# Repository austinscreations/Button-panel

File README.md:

# Button-panel
Low cost RGB button panel for home automation - based off superhouse.tv switch setup

After seeing the new RGB switch panels that jon from superhouse.tv is making the thing that has been noted is the switches cost a fair bit of money. 

I thought it might be possible to 3d print parts and use clear acrylic tubing / rod to create low cost versions of teh panels.
To start I've designed two PCB's one has 4 leds per button to emulate teh current ring light buttons
the second version uses one center led for a cenetr lighting in the button - acyrlic rod would be inserted into a 3d print.

Once I have a chance I plan to produce the pcb and order parts on ebay and create the 3d print assemblies to see what teh cost would be and if it works well.

2021-09-07
added a node-red demo taht hsows all the functions nicely.
added to and bottom photos of pcb along with pinout for RX / TX

2021-07-08
Working full code for type-1 assembly has been added. Now has working button deboucing and outputs teh same json type string as the superhouse.tv LSC project.
New PCB's has been produced and is working correctly with new code - files might need to be updated here...

2021-04-28
Added the latest version. will order parts soon to test the design.
Added a new 3d model for an AUS plate, design is incomplete and will get my hands on a real one to adjust the model as needed.

2021-04-23 
added code that will be used during livestream. haven't got tasmota to control the lights correctly yet; thus will be using custom code

2021-04-22
PCB's arrived which means I'll be doing a livestream of their assembly and testing https://youtu.be/Dpo3wsEXy4c

2021-04-18
Updated 3d files to fit around capacitors and ethernet connector. The 3d files and pcb's will be re-layed out to fix these in the next version. allowing for faster 3d printing, vs having holes / cutouts made.

2021-04-16
I've ordered PCB's to test. 
Created 3d photo of pcb assemblies. Next versions will use esp8266 direct vs D1 mini.
Cost Sheet updated.

2020-12-12
reformated files
added new version 2 which makes the pcb compact - allows for 24mm spacing between each button matching the assembly of teh superhouse button panels - it allso allowed for teh buttons to be centered on a wall plate. wall plate is normal cover / size for single gang north america box
3D step files for each button design assembly has been added - these are untested - no parts on order yet.
future possible version my have the 0.1mm pitch conenctor to match up to the new superhouse tv RGB button assembly.

2020-12-04
updating pcb files as the 1000uf capacitor was the wrong size (footprint is now 10x10mm)
adding photos of the pcb for both versions
added parts list for both versions
added rough cost breakdown of buying parts on ebay

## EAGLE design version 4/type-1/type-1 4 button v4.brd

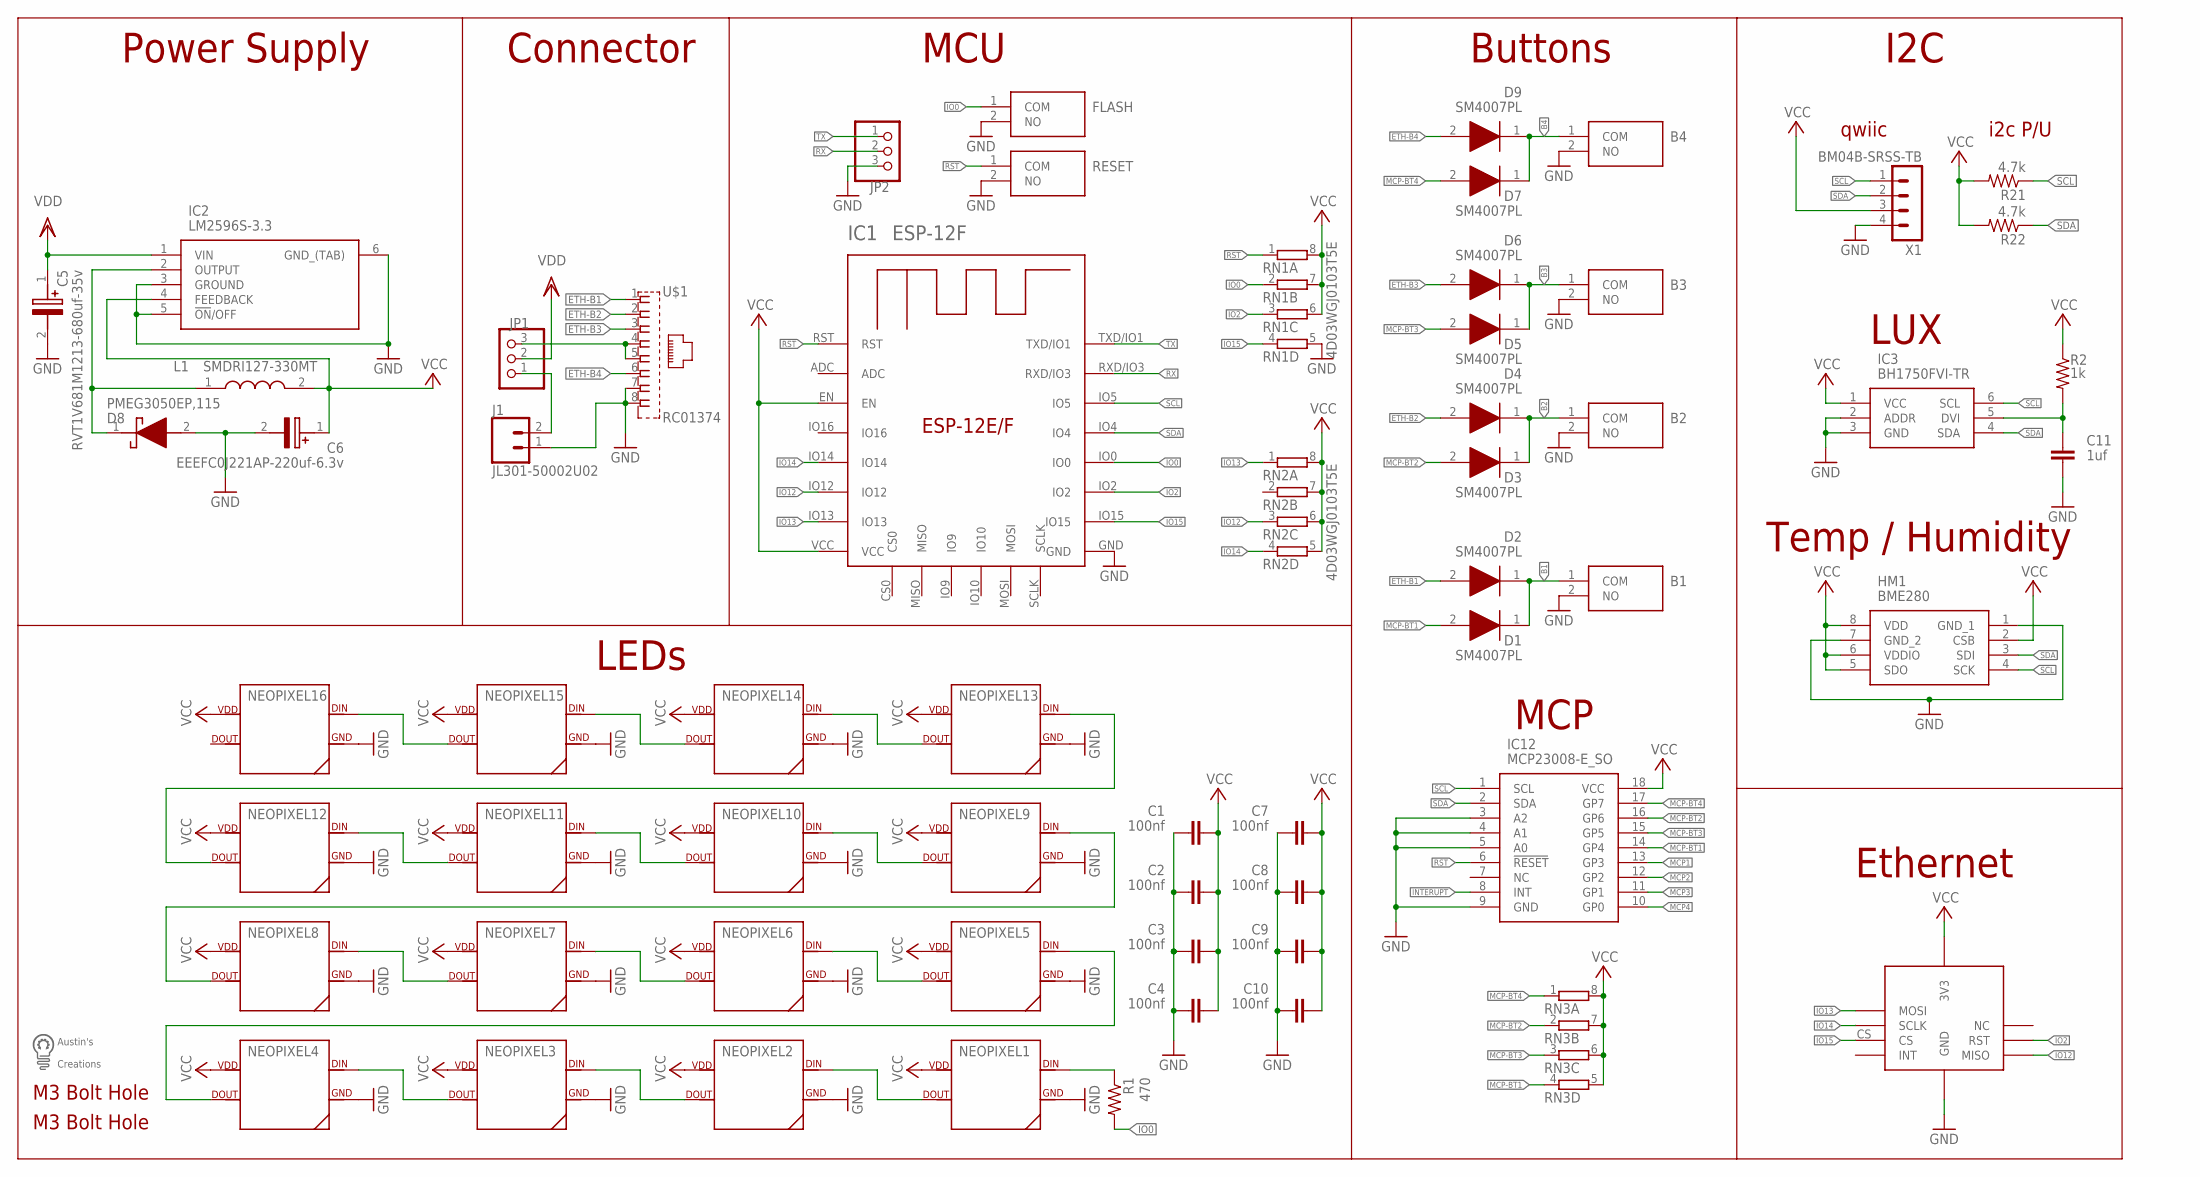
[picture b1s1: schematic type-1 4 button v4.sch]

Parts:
B1, B2, B3, B4: PTS636_SM25F_SMTR_LFS; PTS636SM25FSMTRLFS
C1, C2, C3, C4, C7, C8, C9, C10: 100nf; C0603
C5: RVT1V681M1213-680uf-35v; CAPAE1350X1400N
C6: EEEFC0J221AP-220uf-6.3v; CAPAE830X650N
C11: 1uf; C0603
D1, D2, D3, D4, D5, D6, D7, D9: SM4007PL; SODFL3718X125N
D8: PMEG3050EP,115; PMEG3050EP115
FLASH: PTS636_SM25F_SMTR_LFS; PTS636SM25FSMTRLFS
HM1: BME280
IC1: ESP-12F; ESP-12E
IC2: LM2596S-3.3; TO170P1435X465-6N
IC3: BH1750FVI-TR; WSOF6
IC12: MCP23008-E_SO; SOIC127P1030X265-18N
J1: JL301-50002U02; SCREWTERMINAL-5MM-2
JP1, JP2: PINHD-1X3; 1X03
L1: SMDRI127-330MT; INDPM120120X800N
NEOPIXEL1, NEOPIXEL2, NEOPIXEL3, NEOPIXEL4, NEOPIXEL5, NEOPIXEL6, NEOPIXEL7, NEOPIXEL8, NEOPIXEL9, NEOPIXEL10, NEOPIXEL11, NEOPIXEL12, NEOPIXEL13, NEOPIXEL14, NEOPIXEL15, NEOPIXEL16: SK6812NEOPIXEL5050; SK6812
R1: 470; R0603
R2: 1k; R0603
R21, R22: 4.7k; R0603
RESET: PTS636_SM25F_SMTR_LFS; PTS636SM25FSMTRLFS
RN1, RN2, RN3: 4R-N0603-ARC; 0603-ARC
U$1: RC01374
U$3: W5500MODULE
U$4, U$5: M3BOLTHOLE
U$6: LOGOMED
X1: BM04B-SRSS-TB

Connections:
B1: B1.1 (COM), D1.1 (K), D2.1 (K)
B2: B2.1 (COM), D3.1 (K), D4.1 (K)
B3: B3.1 (COM), D5.1 (K), D6.1 (K)
B4: B4.1 (COM), D7.1 (K), D9.1 (K)
ETH-B1: D2.2 (A), U$1.1
ETH-B2: D4.2 (A), U$1.2
ETH-B3: D6.2 (A), U$1.3
ETH-B4: D9.2 (A), U$1.6
GND: B1.2 (NO), B2.2 (NO), B3.2 (NO), B4.2 (NO), C1.1, C2.1, C3.1, C4.1, C5.2 (-), C6.2 (-), C7.1, C8.1, C9.1, C10.1, C11.2, D8.2 (A), FLASH.2 (NO), HM1.1 (GND_1), HM1.7 (GND_2), IC1.GND, IC2.3 (GROUND), IC2.5 (!ON!/OFF), IC2.6 (GND_(TAB)), IC3.2 (ADDR), IC3.3 (GND), IC12.3 (A2), IC12.4 (A1), IC12.5 (A0), IC12.9 (GND), J1.1, JP2.3, NEOPIXEL1.3 (GND), NEOPIXEL2.3 (GND), NEOPIXEL3.3 (GND), NEOPIXEL4.3 (GND), NEOPIXEL5.3 (GND), NEOPIXEL6.3 (GND), NEOPIXEL7.3 (GND), NEOPIXEL8.3 (GND), NEOPIXEL9.3 (GND), NEOPIXEL10.3 (GND), NEOPIXEL11.3 (GND), NEOPIXEL12.3 (GND), NEOPIXEL13.3 (GND), NEOPIXEL14.3 (GND), NEOPIXEL15.3 (GND), NEOPIXEL16.3 (GND), RESET.2 (NO), RN1.5 (2), U$1.7, U$1.8, U$3.GND1 (GND), U$3.GND2 (GND), U$3.GND3 (GND), X1.4
INTERUPT: IC12.8 (INT)
IO0: FLASH.1 (COM), IC1.IO0, R1.2, RN1.2 (1)
IO2: IC1.IO2, RN1.3 (1), U$3.RST
IO12: IC1.IO12, RN2.3 (1), U$3.MISO
IO13: IC1.IO13, RN2.1, U$3.MOSI
IO14: IC1.IO14, RN2.4 (1), U$3.SCLK
IO15: IC1.IO15, RN1.4 (1), U$3.CS
MCP1: IC12.13 (GP3)
MCP2: IC12.12 (GP2)
MCP3: IC12.11 (GP1)
MCP4: IC12.10 (GP0)
MCP-BT1: D1.2 (A), IC12.14 (GP4), RN3.4 (1)
MCP-BT2: D3.2 (A), IC12.16 (GP6), RN3.2 (1)
MCP-BT3: D5.2 (A), IC12.15 (GP5), RN3.3 (1)
MCP-BT4: D7.2 (A), IC12.17 (GP7), RN3.1
unnamed: NEOPIXEL1.4 (DIN), R1.1
unnamed: NEOPIXEL1.2 (DOUT), NEOPIXEL2.4 (DIN)
unnamed: NEOPIXEL2.2 (DOUT), NEOPIXEL3.4 (DIN)
unnamed: NEOPIXEL3.2 (DOUT), NEOPIXEL4.4 (DIN)
unnamed: NEOPIXEL4.2 (DOUT), NEOPIXEL5.4 (DIN)
unnamed: NEOPIXEL8.2 (DOUT), NEOPIXEL9.4 (DIN)
unnamed: NEOPIXEL12.2 (DOUT), NEOPIXEL13.4 (DIN)
unnamed: NEOPIXEL5.2 (DOUT), NEOPIXEL6.4 (DIN)
unnamed: NEOPIXEL9.2 (DOUT), NEOPIXEL10.4 (DIN)
unnamed: NEOPIXEL13.2 (DOUT), NEOPIXEL14.4 (DIN)
unnamed: NEOPIXEL6.2 (DOUT), NEOPIXEL7.4 (DIN)
unnamed: NEOPIXEL10.2 (DOUT), NEOPIXEL11.4 (DIN)
unnamed: NEOPIXEL14.2 (DOUT), NEOPIXEL15.4 (DIN)
unnamed: NEOPIXEL7.2 (DOUT), NEOPIXEL8.4 (DIN)
unnamed: NEOPIXEL11.2 (DOUT), NEOPIXEL12.4 (DIN)
unnamed: NEOPIXEL15.2 (DOUT), NEOPIXEL16.4 (DIN)
unnamed: JP1.3, U$1.4, U$1.5
unnamed: J1.2, JP1.1
unnamed: D8.1 (K), IC2.2 (OUTPUT), L1.1
unnamed: C11.1, IC3.5 (DVI), R2.2
RST: IC1.RST, IC12.6 (!RESET), RESET.1 (COM), RN1.1
RX: IC1.RXD/IO3, JP2.2
SCL: HM1.4 (SCK), IC1.IO5, IC3.6 (SCL), IC12.1 (SCL), R21.1, X1.1
SDA: HM1.3 (SDI), IC1.IO4, IC3.4 (SDA), IC12.2 (SDA), R22.1, X1.2
TX: IC1.TXD/IO1, JP2.1
VCC: C1.2, C2.2, C3.2, C4.2, C6.1 (+), C7.2, C8.2, C9.2, C10.2, HM1.2 (CSB), HM1.5 (SDO), HM1.6 (VDDIO), HM1.8 (VDD), IC1.EN, IC1.VCC, IC2.4 (FEEDBACK), IC3.1 (VCC), IC12.18 (VCC), L1.2, NEOPIXEL1.1 (VDD), NEOPIXEL2.1 (VDD), NEOPIXEL3.1 (VDD), NEOPIXEL4.1 (VDD), NEOPIXEL5.1 (VDD), NEOPIXEL6.1 (VDD), NEOPIXEL7.1 (VDD), NEOPIXEL8.1 (VDD), NEOPIXEL9.1 (VDD), NEOPIXEL10.1 (VDD), NEOPIXEL11.1 (VDD), NEOPIXEL12.1 (VDD), NEOPIXEL13.1 (VDD), NEOPIXEL14.1 (VDD), NEOPIXEL15.1 (VDD), NEOPIXEL16.1 (VDD), R2.1, R21.2, R22.2, RN1.6 (2), RN1.7 (2), RN1.8 (2), RN2.5 (2), RN2.6 (2), RN2.7 (2), RN2.8 (2), RN3.5 (2), RN3.6 (2), RN3.7 (2), RN3.8 (2), U$3.3V3_1 (3V3), U$3.3V3_2 (3V3), X1.3
VDD: C5.1 (+), IC2.1 (VIN), JP1.2

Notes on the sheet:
Buttons
MCU
Connector
Power Supply
LEDs
4D03WGJ0103T5E
MCP
Ethernet
Temp / Humidity
LUX
i2c P/U
I2C
qwiic

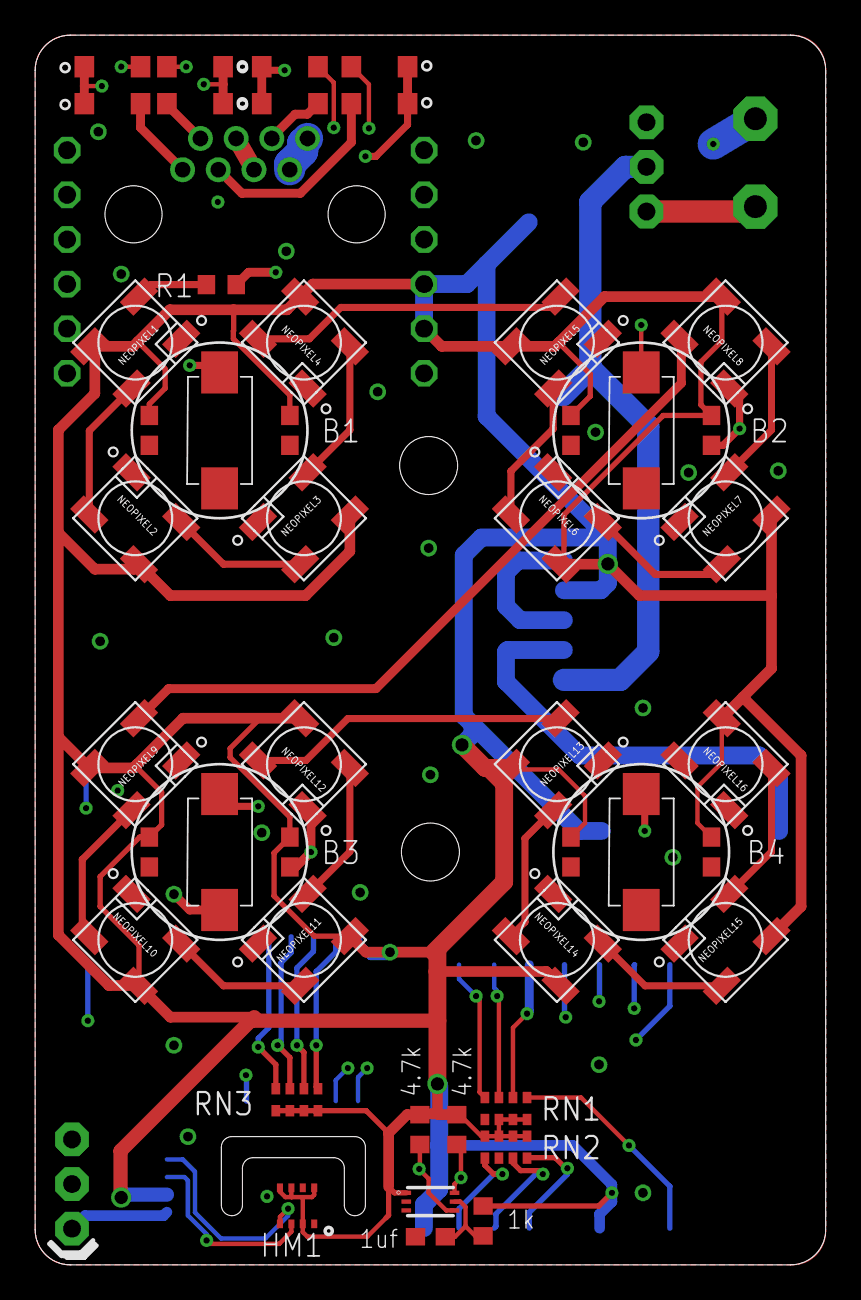
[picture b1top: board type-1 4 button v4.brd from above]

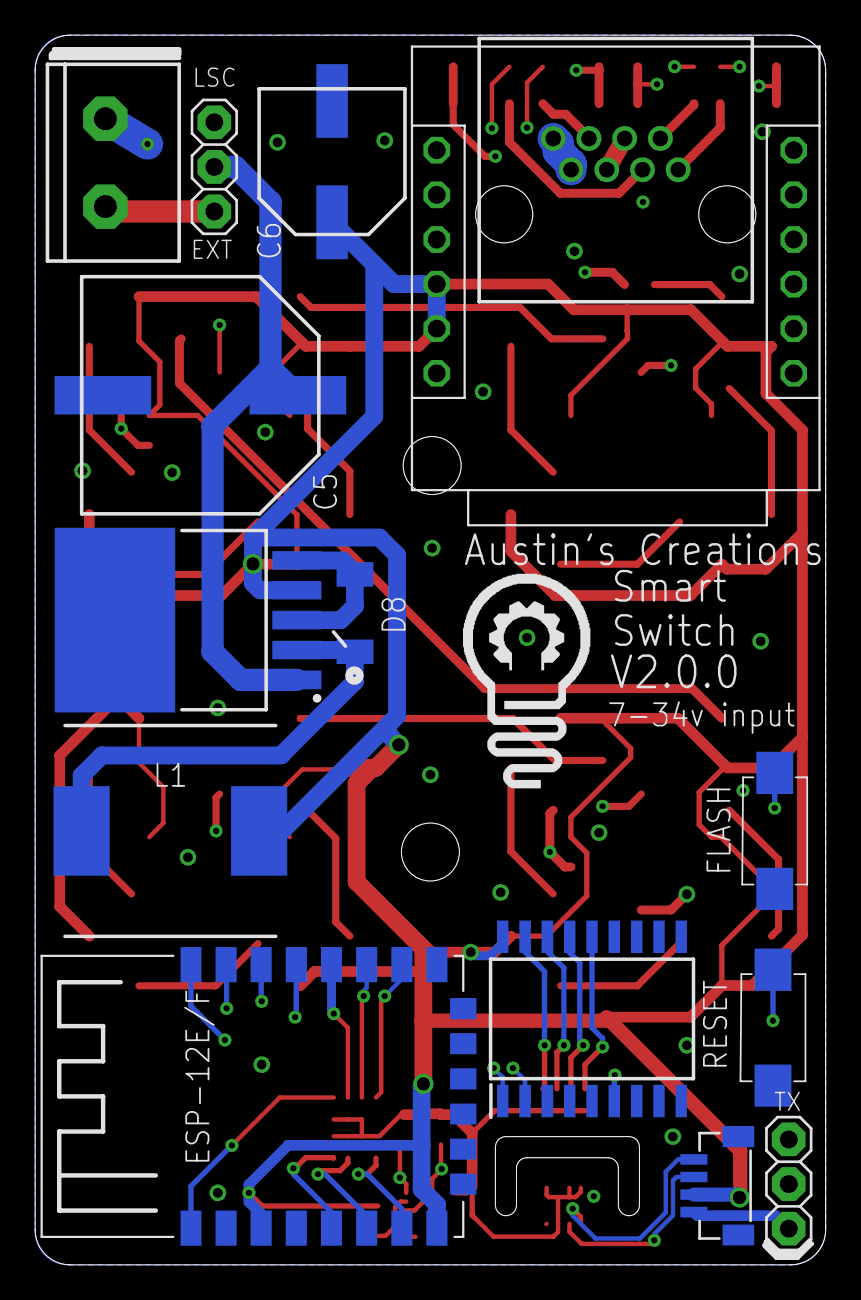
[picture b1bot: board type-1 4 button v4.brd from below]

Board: 4 copper layers, 45.0 x 70.0 mm, 64 parts (16 on the bottom side), 46 nets.

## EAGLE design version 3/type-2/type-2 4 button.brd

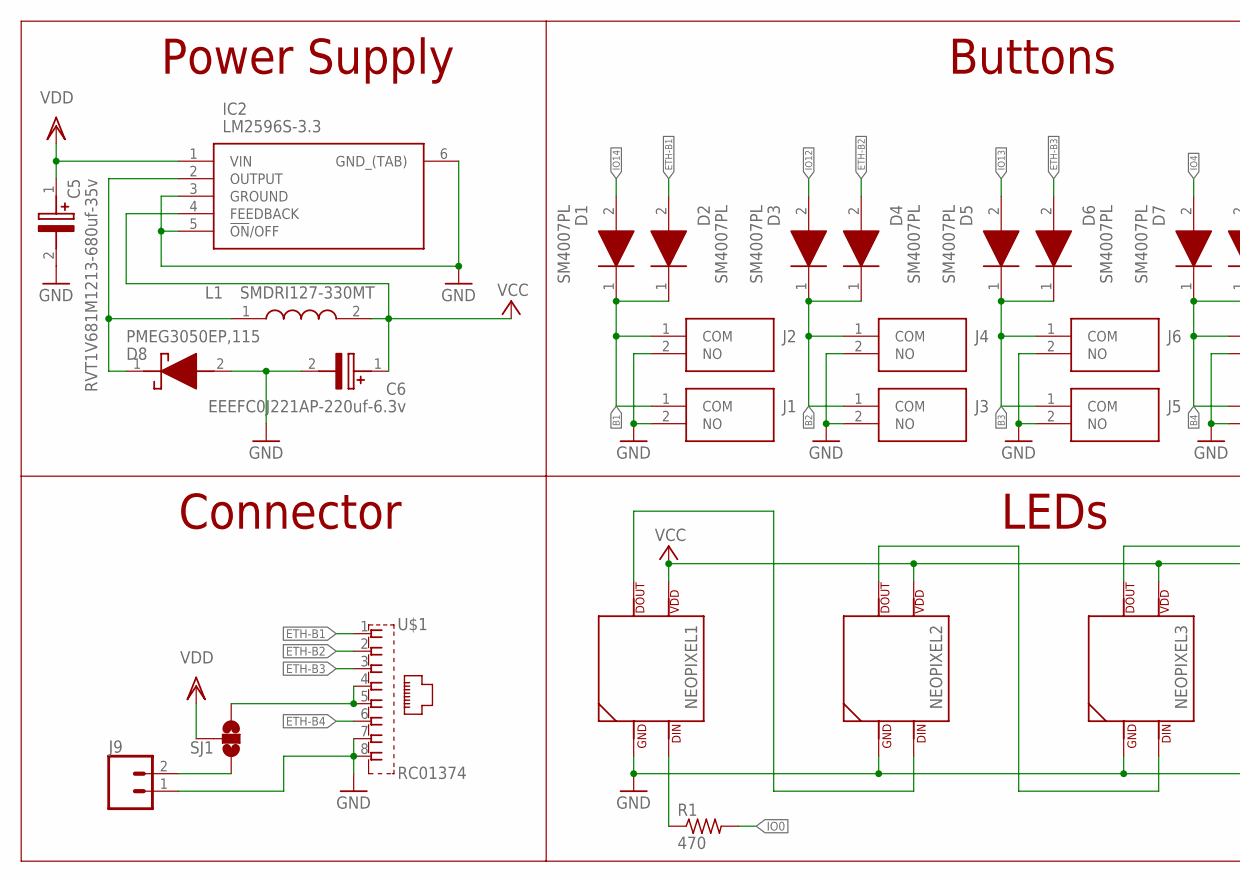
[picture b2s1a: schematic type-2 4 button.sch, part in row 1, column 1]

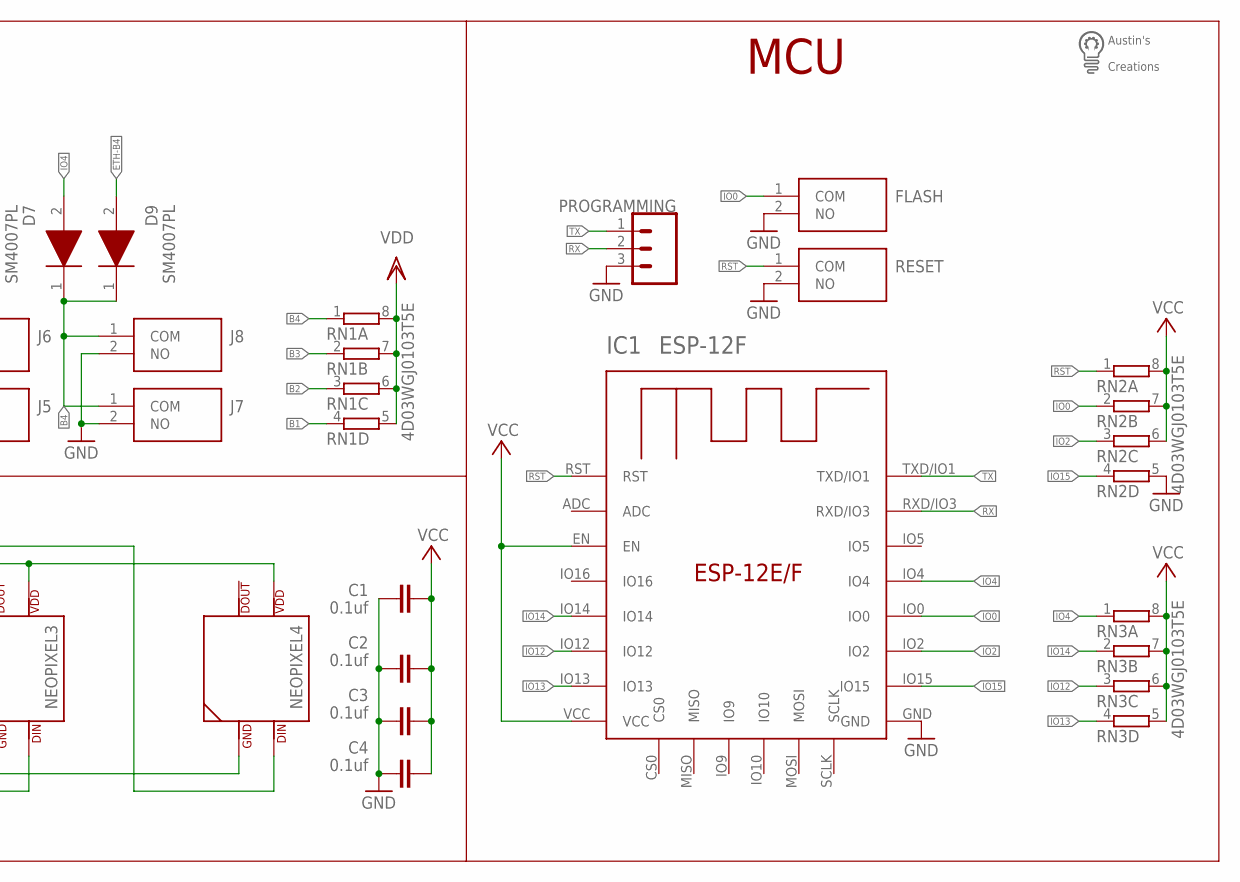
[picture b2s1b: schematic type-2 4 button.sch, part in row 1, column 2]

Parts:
C1, C2, C3, C4: 0.1uf; C0603
C5: RVT1V681M1213-680uf-35v; CAPAE1350X1400N
C6: EEEFC0J221AP-220uf-6.3v; CAPAE830X650N
D1, D2, D3, D4, D5, D6, D7, D9: SM4007PL; SODFL3718X125N
D8: PMEG3050EP,115; PMEG3050EP115
FLASH: PTS636_SM25F_SMTR_LFS; PTS636SM25FSMTRLFS
IC1: ESP-12F; ESP-12E
IC2: LM2596S-3.3; TO170P1435X465-6N
J1, J2, J3, J4, J5, J6, J7, J8: PTS636_SM25F_SMTR_LFS; PTS636SM25FSMTRLFS
J9: CONN_025MM; SCREWTERMINAL-5MM-2
L1: SMDRI127-330MT; INDPM120120X800N
NEOPIXEL1, NEOPIXEL2, NEOPIXEL3, NEOPIXEL4: SK6812NEOPIXEL5050; SK6812
PROGRAMMING: 455-1750-1-ND; 1X03
R1: 470; R0603
RESET: PTS636_SM25F_SMTR_LFS; PTS636SM25FSMTRLFS
RN1, RN2, RN3: 4R-N0603-ARC; 0603-ARC
SJ1: SOLDERJUMPER_2WAYPASTE1&2; SJ_3_PASTE1&2
U$1: RC01374
U$2: LOGO

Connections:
B1: D1.1 (K), D2.1 (K), J1.1 (COM), J2.1 (COM), RN1.4 (1)
B2: D3.1 (K), D4.1 (K), J3.1 (COM), J4.1 (COM), RN1.3 (1)
B3: D5.1 (K), D6.1 (K), J5.1 (COM), J6.1 (COM), RN1.2 (1)
B4: D7.1 (K), D9.1 (K), J7.1 (COM), J8.1 (COM), RN1.1
ETH-B1: D2.2 (A), U$1.1
ETH-B2: D4.2 (A), U$1.2
ETH-B3: D6.2 (A), U$1.3
ETH-B4: D9.2 (A), U$1.6
GND: C1.1, C2.1, C3.1, C4.1, C5.2 (-), C6.2 (-), D8.2 (A), FLASH.2 (NO), IC1.GND, IC2.3 (GROUND), IC2.5 (!ON!/OFF), IC2.6 (GND_(TAB)), J1.2 (NO), J2.2 (NO), J3.2 (NO), J4.2 (NO), J5.2 (NO), J6.2 (NO), J7.2 (NO), J8.2 (NO), J9.1, NEOPIXEL1.3 (GND), NEOPIXEL2.3 (GND), NEOPIXEL3.3 (GND), NEOPIXEL4.3 (GND), PROGRAMMING.3, RESET.2 (NO), RN2.5 (2), U$1.7, U$1.8
IO0: FLASH.1 (COM), IC1.IO0, R1.2, RN2.2 (1)
IO2: IC1.IO2, RN2.3 (1)
IO4: D7.2 (A), IC1.IO4, RN3.1
IO12: D3.2 (A), IC1.IO12, RN3.3 (1)
IO13: D5.2 (A), IC1.IO13, RN3.4 (1)
IO14: D1.2 (A), IC1.IO14, RN3.2 (1)
IO15: IC1.IO15, RN2.4 (1)
unnamed: NEOPIXEL1.2 (DOUT), NEOPIXEL2.4 (DIN)
unnamed: NEOPIXEL2.2 (DOUT), NEOPIXEL3.4 (DIN)
unnamed: NEOPIXEL3.2 (DOUT), NEOPIXEL4.4 (DIN)
unnamed: NEOPIXEL1.4 (DIN), R1.1
unnamed: J9.2, SJ1.3
unnamed: SJ1.1, U$1.4, U$1.5
unnamed: D8.1 (K), IC2.2 (OUTPUT), L1.1
RST: IC1.RST, RESET.1 (COM), RN2.1
RX: IC1.RXD/IO3, PROGRAMMING.2
TX: IC1.TXD/IO1, PROGRAMMING.1
VCC: C1.2, C2.2, C3.2, C4.2, C6.1 (+), IC1.EN, IC1.VCC, IC2.4 (FEEDBACK), L1.2, NEOPIXEL1.1 (VDD), NEOPIXEL2.1 (VDD), NEOPIXEL3.1 (VDD), NEOPIXEL4.1 (VDD), RN2.6 (2), RN2.7 (2), RN2.8 (2), RN3.5 (2), RN3.6 (2), RN3.7 (2), RN3.8 (2)
VDD: C5.1 (+), IC2.1 (VIN), RN1.5 (2), RN1.6 (2), RN1.7 (2), RN1.8 (2), SJ1.2

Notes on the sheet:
Buttons
LEDs
Connector
MCU
Power Supply
4D03WGJ0103T5E

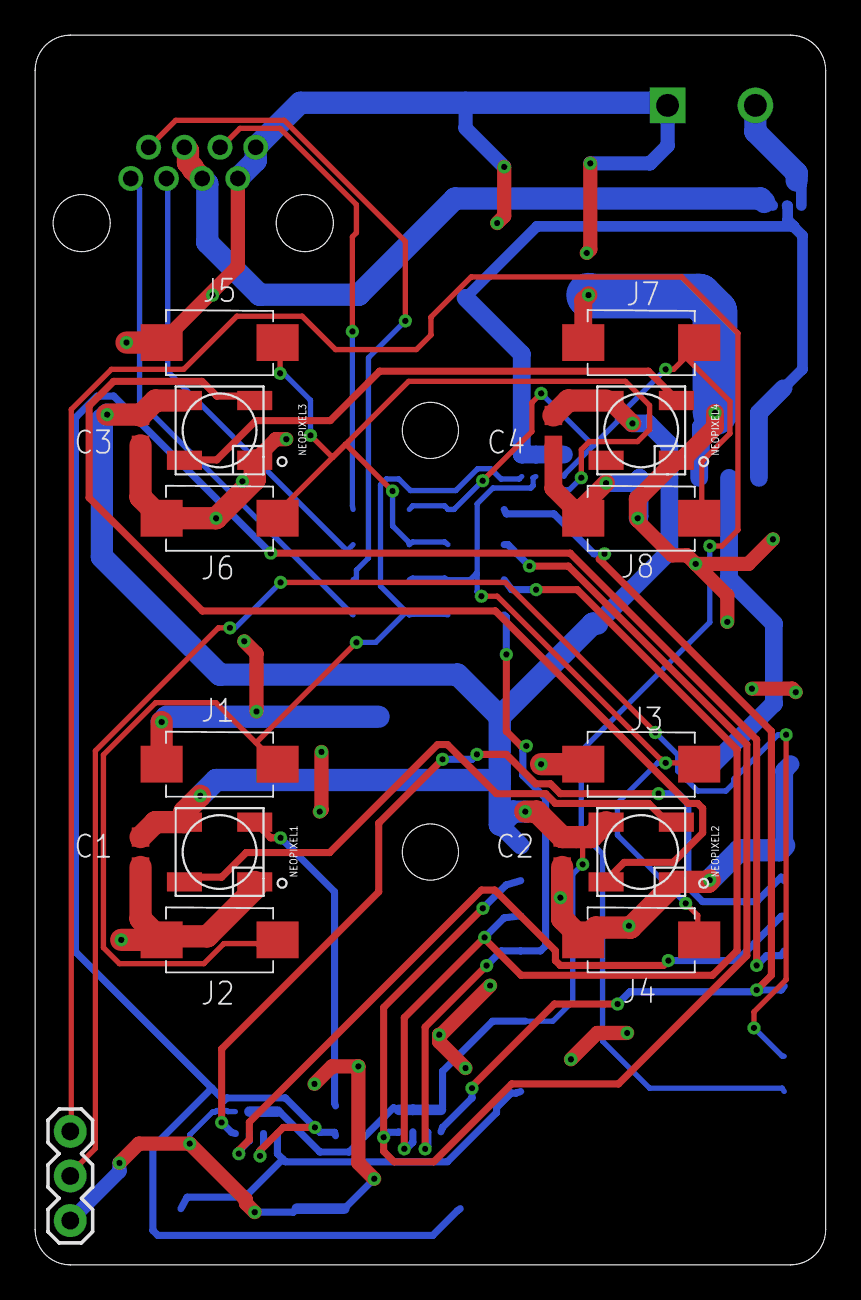
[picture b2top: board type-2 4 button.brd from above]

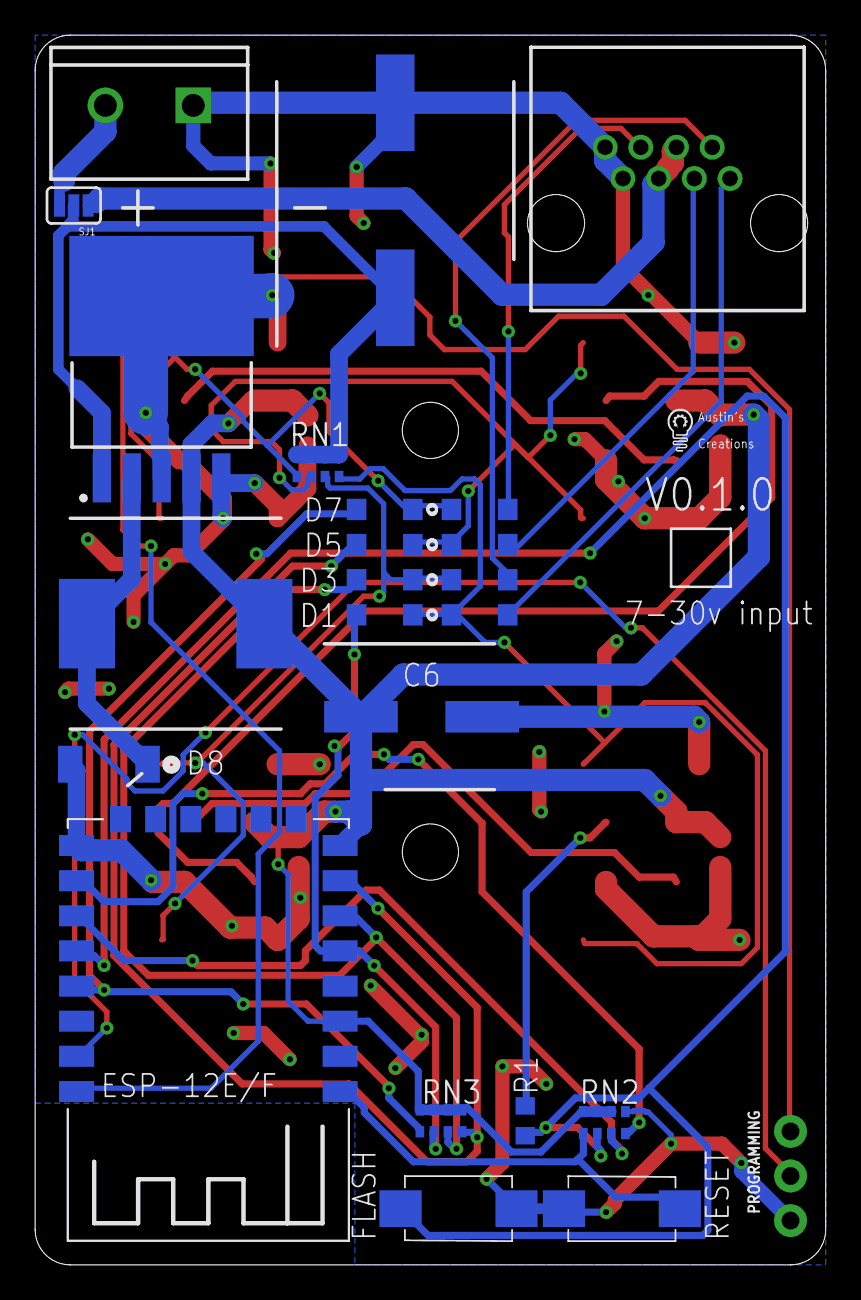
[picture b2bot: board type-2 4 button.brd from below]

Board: 2 copper layers, 45.0 x 70.0 mm, 41 parts (24 on the bottom side), 28 nets.

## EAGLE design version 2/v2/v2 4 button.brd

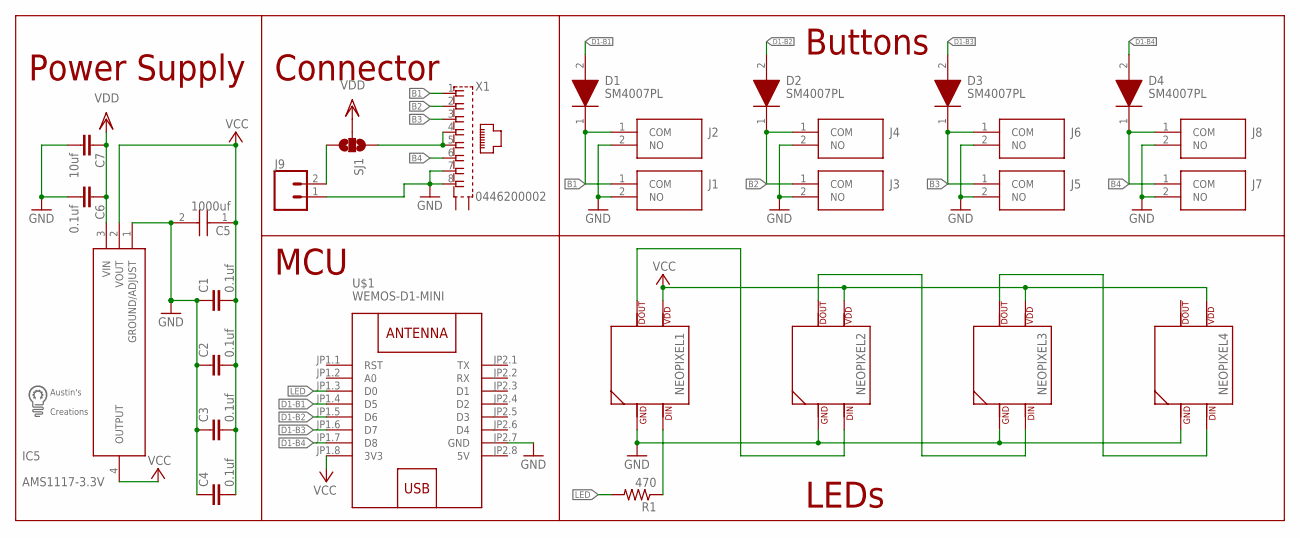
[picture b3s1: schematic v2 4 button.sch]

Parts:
C1, C2, C3, C4, C6: 0.1uf; C0603
C5: 1000uf; CAPAE1030X1050N
C7: 10uf; C0603
D1, D2, D3, D4: SM4007PL; SODFL3718X125N
IC5: AMS1117-3.3V; SOT229P700X180-4N
J1, J2, J3, J4, J5, J6, J7, J8: PTS636_SM25F_SMTR_LFS; PTS636SM25FSMTRLFS
J9: CONN_025MM; SCREWTERMINAL-5MM-2
NEOPIXEL1, NEOPIXEL2, NEOPIXEL3, NEOPIXEL4: SK6812NEOPIXEL5050; SK6812
R1: 470; R0603
SJ1: SOLDERJUMPER_2WAYPASTE1&2; SJ_3_PASTE1&2
U$1: WEMOS-D1-MINI
U$2: LOGO
X1: 0446200002

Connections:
5V: U$1.JP2.8 (5V)
B1: D1.1 (K), J1.1 (COM), J2.1 (COM), X1.1
B2: D2.1 (K), J3.1 (COM), J4.1 (COM), X1.2
B3: D3.1 (K), J5.1 (COM), J6.1 (COM), X1.3
B4: D4.1 (K), J7.1 (COM), J8.1 (COM), X1.6
D1-B1: D1.2 (A), U$1.JP1.4 (D5)
D1-B2: D2.2 (A), U$1.JP1.5 (D6)
D1-B3: D3.2 (A), U$1.JP1.6 (D7)
D1-B4: D4.2 (A), U$1.JP1.7 (D8)
GND: C1.1, C2.1, C3.1, C4.1, C5.2 (-), C6.2, C7.2, IC5.1 (GROUND/ADJUST), J1.2 (NO), J2.2 (NO), J3.2 (NO), J4.2 (NO), J5.2 (NO), J6.2 (NO), J7.2 (NO), J8.2 (NO), J9.1, NEOPIXEL1.3 (GND), NEOPIXEL2.3 (GND), NEOPIXEL3.3 (GND), NEOPIXEL4.3 (GND), U$1.JP2.7 (GND), X1.7, X1.8
LED: R1.2, U$1.JP1.3 (D0)
unnamed: NEOPIXEL1.2 (DOUT), NEOPIXEL2.4 (DIN)
unnamed: NEOPIXEL2.2 (DOUT), NEOPIXEL3.4 (DIN)
unnamed: NEOPIXEL3.2 (DOUT), NEOPIXEL4.4 (DIN)
unnamed: SJ1.1, X1.4, X1.5
unnamed: NEOPIXEL1.4 (DIN), R1.1
unnamed: J9.2, SJ1.3
VCC: C1.2, C2.2, C3.2, C4.2, C5.1 (+), IC5.2 (VOUT), IC5.4 (OUTPUT), NEOPIXEL1.1 (VDD), NEOPIXEL2.1 (VDD), NEOPIXEL3.1 (VDD), NEOPIXEL4.1 (VDD), U$1.JP1.8 (3V3)
VDD: C6.1, C7.1, IC5.3 (VIN), SJ1.2

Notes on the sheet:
Buttons
LEDs
Connector
MCU
Power Supply

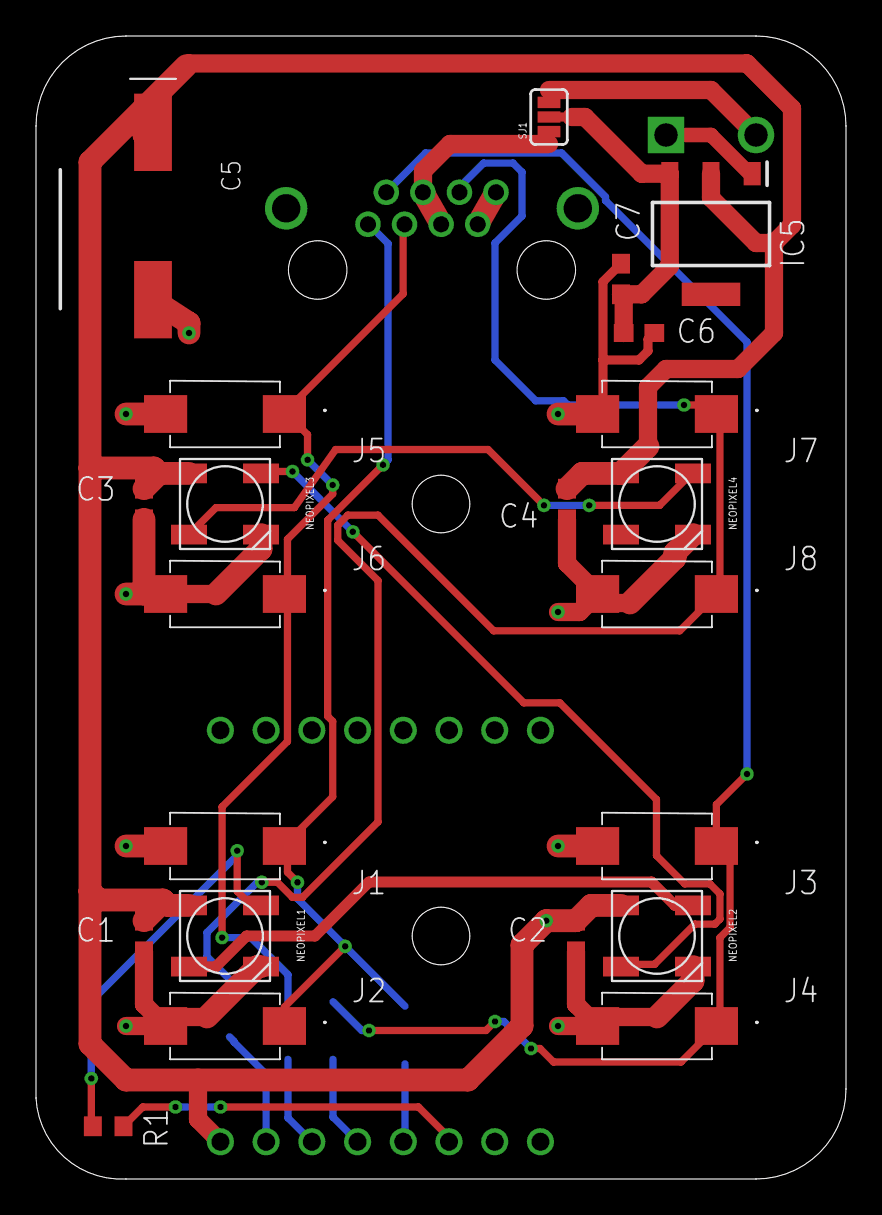
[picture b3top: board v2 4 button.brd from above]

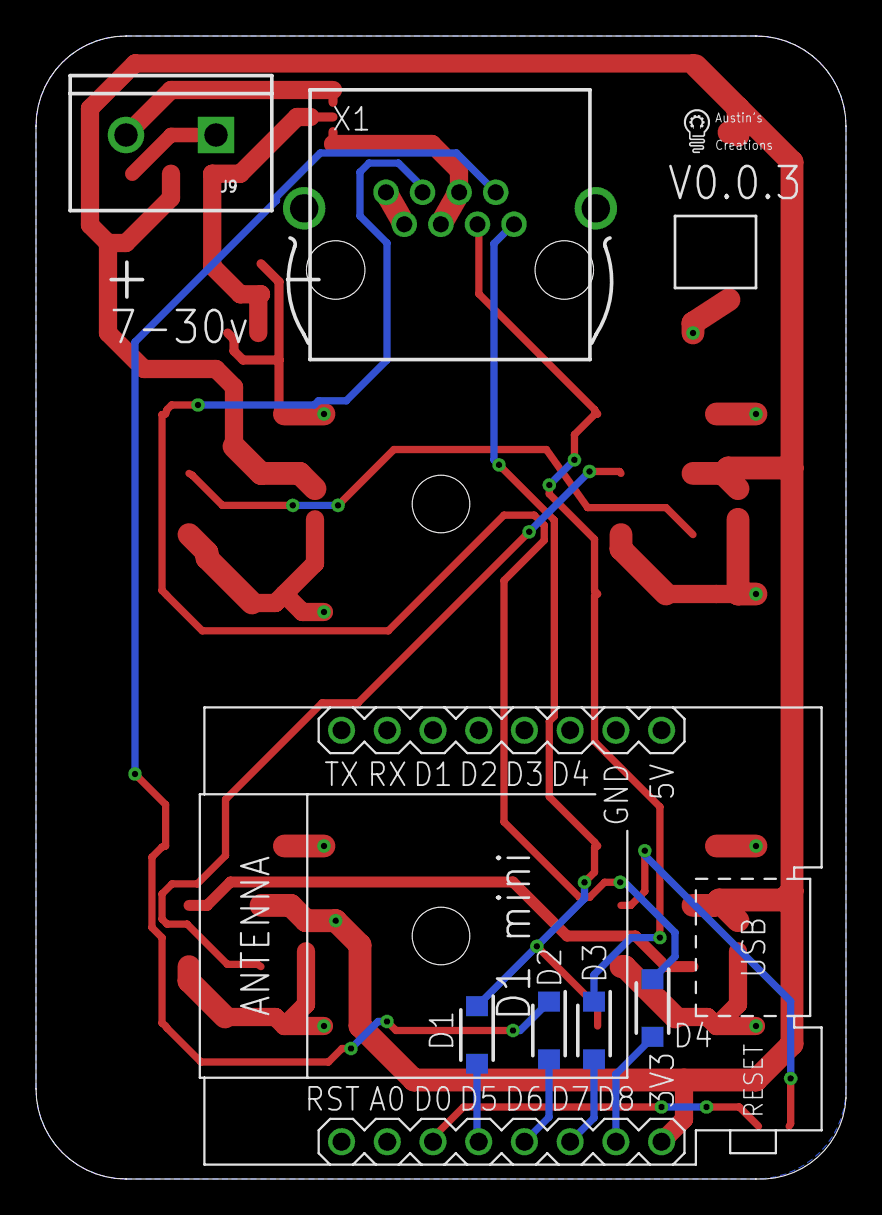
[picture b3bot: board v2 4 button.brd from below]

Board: 2 copper layers, 45.0 x 63.5 mm, 30 parts (8 on the bottom side), 18 nets.

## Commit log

2021-07-01 Create code
2021-07-08 Add files via upload
    trying to get button detection working - this code has an issue with call back - but the serial output within the library is showing correct button presses.
2021-07-08 Add files via upload
    fully working.
2021-07-08 Rename config - example.h to config.h
2021-09-07 Add files via upload
    adding demo of node-red

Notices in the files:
parts and their libraries:
diy-modules: Released under the Creative Commons Attribution 4.0 International License: http://creativecommons.org/licenses/by/4.0
SparkFun-Retired: Licensing: Creative Commons ShareAlike 4.0 International - https://creativecommons.org/licenses/by-sa/4.0
